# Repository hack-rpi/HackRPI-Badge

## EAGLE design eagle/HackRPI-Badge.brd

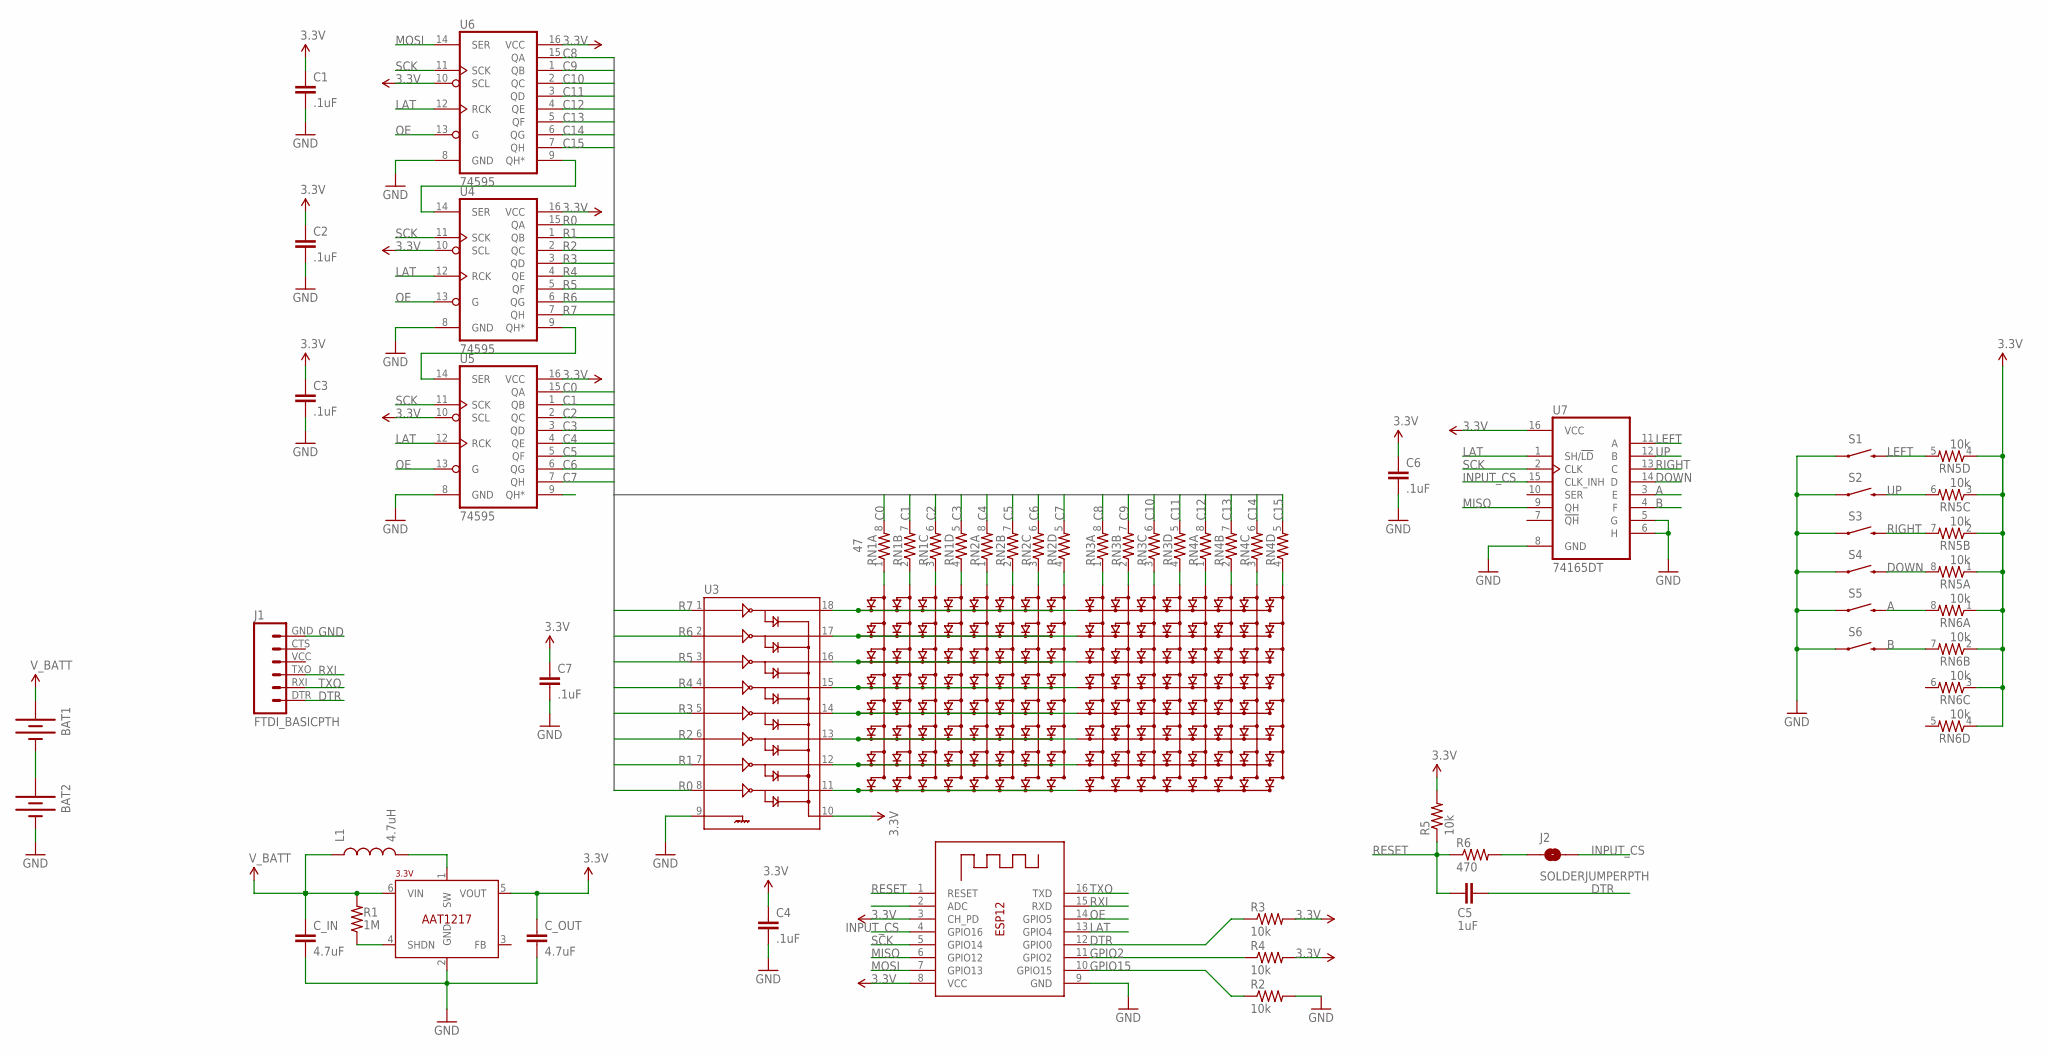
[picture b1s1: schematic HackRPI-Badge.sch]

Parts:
BAT1, BAT2: BATTERYAAA; BATTERY-AAA; PARTNO BK-82
C1, C2, C3, C4, C6, C7: .1uF; 0603-CAP; PARTNO CC0603ZRY5V9BB104
C5: 1uF; 0603-CAP
C_IN: 4.7uF; 0805; PARTNO CL21A475KQFNNNG
C_OUT: 4.7uF; 0805; PARTNO CL21A475KQFNNNG
J1: FTDI_BASICPTH; FTDI_BASIC
J2: SOLDERJUMPERPTH; SJ_2S-PTH
L1: 4.7uH; 1007; PARTNO CIG22L4R7MNE
LED_LEFT: 8X8LEDMATRIX_COLUMN_CATHODELDM-13488MI; 32MM_LEDMATRIX; PARTNO LDM-13488MI
LED_RIGHT: 8X8LEDMATRIX_COLUMN_CATHODELDM-13488MI; 32MM_LEDMATRIX; PARTNO LDM-13488MI
R1: 1M; 0603-RES; PARTNO RC0603JR-071ML
R2, R3, R4, R5: 10k; 0603-RES; PARTNO RC0603JR-0710KL
R6: 470; 0603-RES; PARTNO RC0603JR-07470RL
RN1, RN2, RN3, RN4: 47; 0603-ARV; PARTNO YC164-JR-0747RL
RN5, RN6: 10k; 0603-ARV; PARTNO 742C083103JP
S1, S2, S3, S4, S5, S6: SWITCH-MOMENTARY-2PTH; TACTILE-PTH; PARTNO 1825910-6
U1: ESP-12; PARTNO 2491
U2: 3.3V; SOT23-6; PARTNO AAT1217ICA-3.3-T1
U3: ULN2803SOICW; SO18L; PARTNO ULN2803AFWG,C,EL
U4, U5, U6: 74595; TSSOP16; PARTNO 74HC595PW,118
U7: 74165DT; TSSOP16; PARTNO MC74HC165ADTR2G

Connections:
3.3V: C1.1, C2.1, C3.1, C4.1, C6.1, C7.1, C_OUT.1, R3.2, R4.2, R5.2, RN5.1, RN5.2 (1), RN5.3 (1), RN5.4 (1), RN6.1, RN6.2 (1), RN6.3 (1), RN6.4 (1), U1.3 (CH_PD), U1.8 (VCC), U2.5 (VOUT), U3.10, U4.10 (SCL), U4.16 (VCC), U5.10 (SCL), U5.16 (VCC), U6.10 (SCL), U6.16 (VCC), U7.16 (VCC)
A: RN6.8 (2), S5.3 (2), U7.3 (E)
B: RN6.7 (2), S6.3 (2), U7.4 (F)
C0: RN1.8 (2), U5.15 (QA)
C1: RN1.7 (2), U5.1 (QB)
C2: RN1.6 (2), U5.2 (QC)
C3: RN1.5 (2), U5.3 (QD)
C4: RN2.8 (2), U5.4 (QE)
C5: RN2.7 (2), U5.5 (QF)
C6: RN2.6 (2), U5.6 (QG)
C7: RN2.5 (2), U5.7 (QH)
C8: RN3.8 (2), U6.15 (QA)
C9: RN3.7 (2), U6.1 (QB)
C10: RN3.6 (2), U6.2 (QC)
C11: RN3.5 (2), U6.3 (QD)
C12: RN4.8 (2), U6.4 (QE)
C13: RN4.7 (2), U6.5 (QF)
C14: RN4.6 (2), U6.6 (QG)
C15: RN4.5 (2), U6.7 (QH)
DOWN: RN5.8 (2), S4.3 (2), U7.14 (D)
DTR: C5.2, J1.DTR (1), R3.1, U1.12 (GPIO0)
GND: BAT2.GND@1 (-), C1.2, C2.2, C3.2, C4.2, C6.2, C7.2, C_IN.2, C_OUT.2, J1.GND (6), R2.2, S1.1, S2.1, S3.1, S4.1, S5.1, S6.1, U1.9 (GND), U2.2 (GND), U3.9, U4.8 (GND), U5.8 (GND), U6.8 (GND), U7.5 (G), U7.6 (H), U7.8 (GND)
GPIO2: R4.1, U1.11 (GPIO2)
GPIO15: R2.1, U1.10 (GPIO15)
INPUT_CS: J2.2, U1.4 (GPIO16), U7.15 (CLK_INH)
LAT: U1.13 (GPIO4), U4.12 (RCK), U5.12 (RCK), U6.12 (RCK), U7.1 (SH/!LD)
LEFT: RN5.5 (2), S1.3 (2), U7.11 (A)
MISO: U1.6 (GPIO12), U7.9 (QH)
MOSI: U1.7 (GPIO13), U6.14 (SER)
unnamed: J2.1, R6.2
unnamed: LED_LEFT.13 (C1), RN1.1
unnamed: LED_LEFT.3 (C2), RN1.2 (1)
unnamed: L1.2, U2.1 (SW)
unnamed: R1.1, U2.4 (SHDN)
unnamed: LED_LEFT.9 (R1), LED_RIGHT.9 (R1), U3.18
unnamed: LED_LEFT.4 (C3), RN1.3 (1)
unnamed: LED_LEFT.10 (C4), RN1.4 (1)
unnamed: LED_LEFT.6 (C5), RN2.1
unnamed: LED_LEFT.11 (C6), RN2.2 (1)
unnamed: LED_LEFT.15 (C7), RN2.3 (1)
unnamed: LED_LEFT.16 (C8), RN2.4 (1)
unnamed: LED_LEFT.14 (R2), LED_RIGHT.14 (R2), U3.17
unnamed: LED_LEFT.8 (R3), LED_RIGHT.8 (R3), U3.16
unnamed: LED_LEFT.12 (R4), LED_RIGHT.12 (R4), U3.15
unnamed: LED_LEFT.1 (R5), LED_RIGHT.1 (R5), U3.14
unnamed: LED_LEFT.7 (R6), LED_RIGHT.7 (R6), U3.13
unnamed: LED_LEFT.2 (R7), LED_RIGHT.2 (R7), U3.12
unnamed: LED_LEFT.5 (R8), LED_RIGHT.5 (R8), U3.11
unnamed: U4.9 (QH*), U5.14 (SER)
unnamed: U4.14 (SER), U6.9 (QH*)
unnamed: LED_RIGHT.13 (C1), RN3.1
unnamed: LED_RIGHT.3 (C2), RN3.2 (1)
unnamed: LED_RIGHT.4 (C3), RN3.3 (1)
unnamed: LED_RIGHT.10 (C4), RN3.4 (1)
unnamed: LED_RIGHT.6 (C5), RN4.1
unnamed: LED_RIGHT.11 (C6), RN4.2 (1)
unnamed: LED_RIGHT.15 (C7), RN4.3 (1)
unnamed: LED_RIGHT.16 (C8), RN4.4 (1)
unnamed: BAT1.GND@1 (-), BAT2.PWR@1 (+)
OE: U1.14 (GPIO5), U4.13 (G), U5.13 (G), U6.13 (G)
R0: U3.8, U4.15 (QA)
R1: U3.7, U4.1 (QB)
R2: U3.6, U4.2 (QC)
R3: U3.5, U4.3 (QD)
R4: U3.4, U4.4 (QE)
R5: U3.3, U4.5 (QF)
R6: U3.2, U4.6 (QG)
R7: U3.1, U4.7 (QH)
RESET: C5.1, R5.1, R6.1, U1.1 (RESET)
RIGHT: RN5.7 (2), S3.3 (2), U7.13 (C)
RXI: J1.TXO (3), U1.15 (RXD)
SCK: U1.5 (GPIO14), U4.11 (SCK), U5.11 (SCK), U6.11 (SCK), U7.2 (CLK)
TXO: J1.RXI (2), U1.16 (TXD)
UP: RN5.6 (2), S2.3 (2), U7.12 (B)
V_BATT: BAT1.PWR@1 (+), C_IN.1, L1.1, R1.2, U2.6 (VIN)

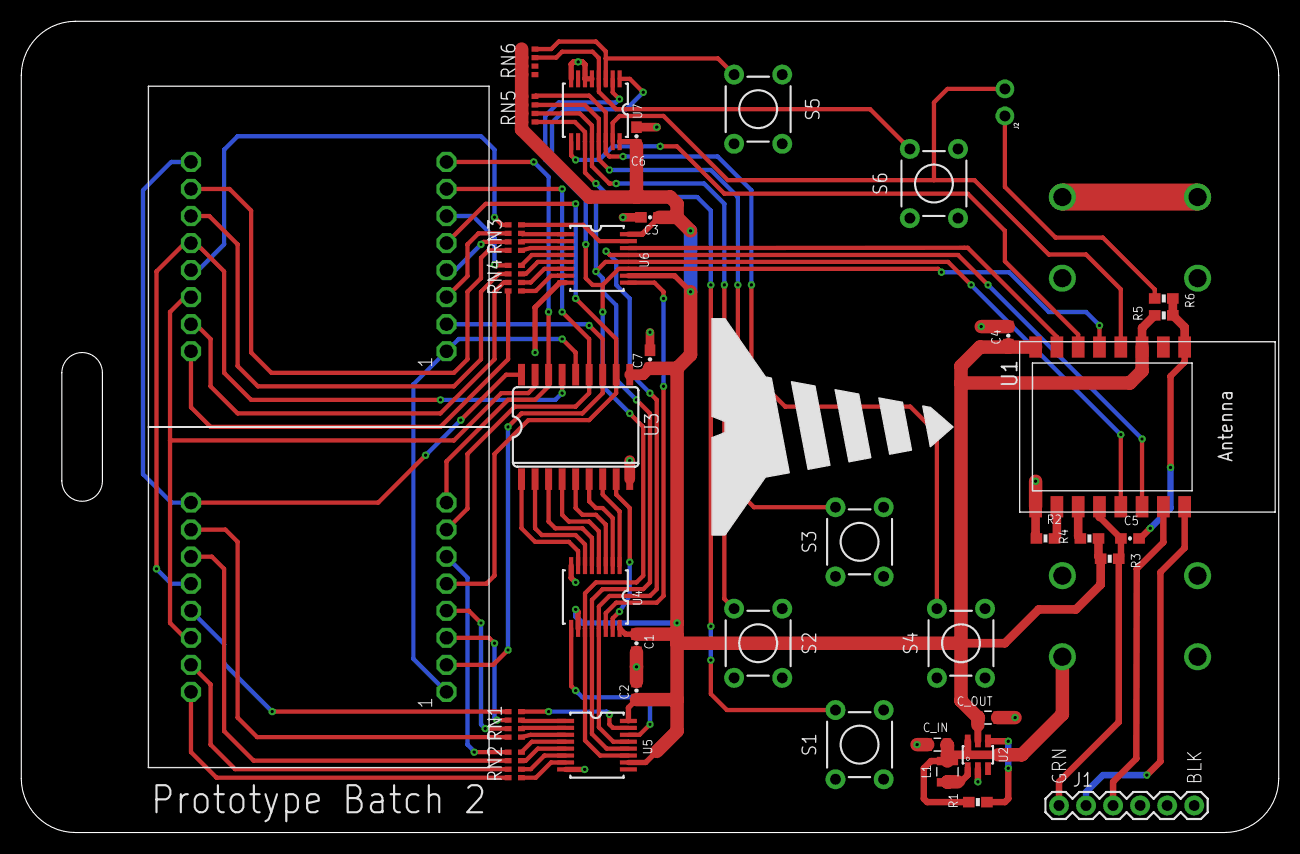
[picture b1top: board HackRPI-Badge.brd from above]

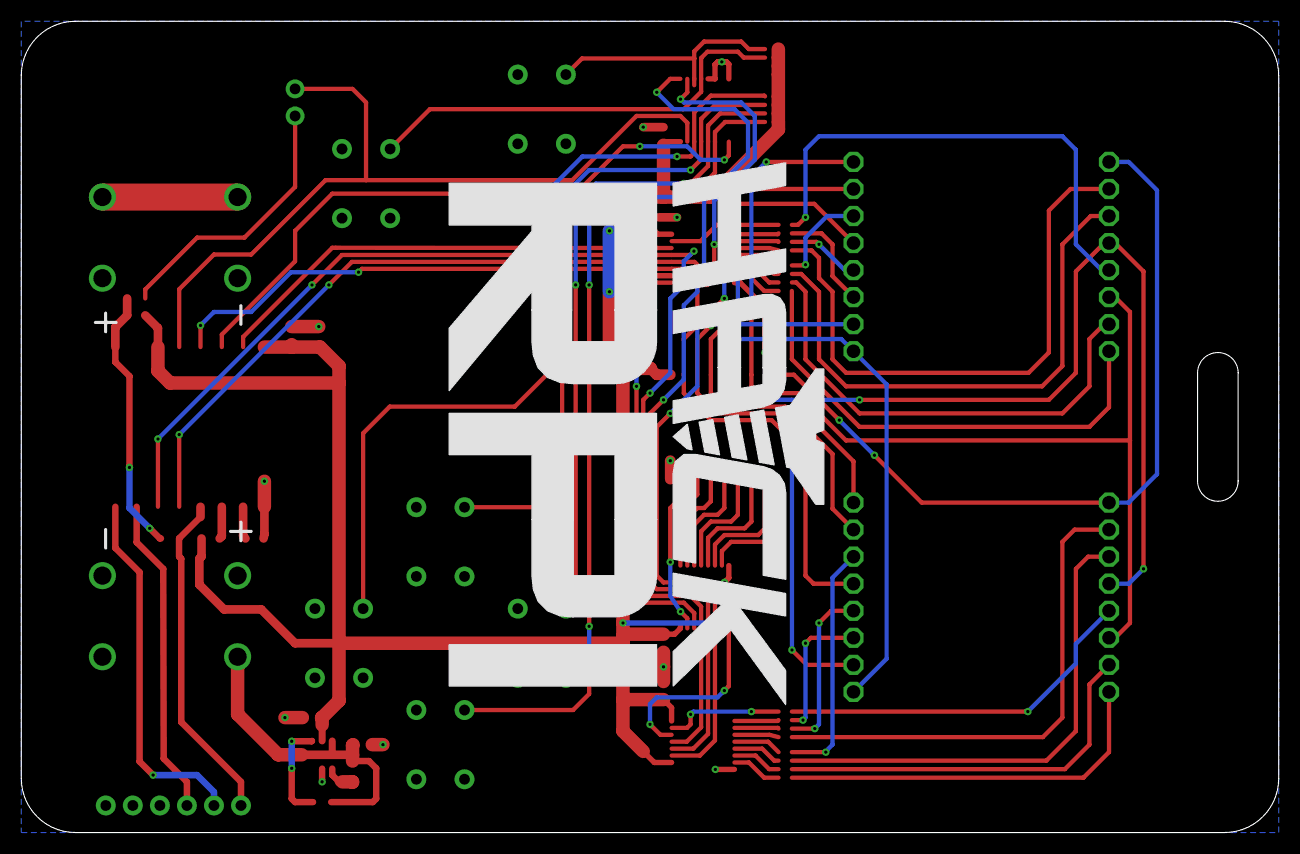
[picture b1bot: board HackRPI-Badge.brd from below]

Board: 2 copper layers, 118.1 x 76.2 mm, 43 parts (3 on the bottom side), 75 nets.

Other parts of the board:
U$1: HACKRPI-LOGO
U$2: HACKRPI-SCREW

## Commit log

2016-08-25 Moved resistor nets to ensure constant LED brightness, added serial connector, added 74HC165 for input
2016-08-31 Updated part names, misc work
2016-09-01 Placed components on board, routed LED matrices and output shift registers, rounded corners of board
2016-09-06 Finished laying out/routing first revision of board
2016-09-12 Added flash memory for storing certificates, named some nets to be more clear
2016-09-12 Fixed 74165 sck pin connection, updated gitignore to ignore lock files
2016-09-12 Generated gerbers for board
2016-09-12 Added prototype batch designation to board and regenerated gerbers
2016-09-16 Added bom partno attributes to all parts
2016-09-16 Fixed bom part numbers
2016-09-23 Moved all eagle files to an eagle folder
2016-09-23 Fixed AAT1217 pinout and modified board for correct pinout
2016-09-24 Started work on badge library
2016-09-24 Fixed ESP12 pinout
2016-09-24 Implemented LED display control in badge library, added demo code
2016-09-24 Added file to demo with wifi ssid/pass and updated its index to ignore changes (to prevent commiting wifi passwords
2016-09-25 Created typeset bitmap and implemented text drawing
2016-09-25 Fixed writeText function, added missing ']' character in typeset, added function to measure text width, updated demo code
2016-09-26 Fixed OTA updating in demo code
2016-09-26 Added Doxyfile and generated doxygen documentation
2016-09-26 Changed doxygen output directory to docs
2016-09-26 Moved docs directory to root directory of repository
2016-09-26 Regenerated doxygen documentation
2016-09-26 Added typeset files to generated documentation files
2016-09-27 Fixed layout to use correct esp8266 pinout
2016-09-27 Tented vias, added HackRPI logo on back of board
2016-09-27 Added HackRPI screw on front of board, removed temporary HackRPI text
2016-09-27 Changed board batch text to batch 2
2016-09-27 Removed external flash memory from badge (ESP-12 module has plenty of flash onboard)
2016-09-27 Finished implementing per-pixel brightness (16 discrete brightnesses)
2016-09-27 Began work on implementing input shift register reading
2016-09-29 Moved batteries away from eachother
2016-09-29 Moved buttons, changed some pin assignments, added input shift register source
2016-09-30 Got button input working (needs code cleanup)
2016-10-04 Tied GPIO0 to DTR, changed deep sleep jumper to normally open (necessary for programming)
2016-10-05 Moved ESP module to center-bottom of badge and made the badge smaller, re-routed traces after resizing badge
2016-10-05 Updated logo and screw on board to have width (prevents errors during gerber generation), regenerated gerbers
2016-10-06 Fixed badge corner not being flush with edge
2016-10-06 Regenerated gerbers
2016-10-06 Another corner fix
2016-10-06 Fixed LED matrix name typo, updated BOM info for a capacitor

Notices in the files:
parts and their libraries:
SparkFun-Aesthetics: Licensing: Creative Commons ShareAlike 4.0 International - https://creativecommons.org/licenses/by-sa/4.0
